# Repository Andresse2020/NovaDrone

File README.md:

# NovaDrone

Copyright © 2025 Andresse Brisel BASSINGA
Licensed under CERN Open Hardware Licence v2 – Weakly Reciprocal (CERN-OHL-W)

This project provides a complete hardware design for a professional UAV Quadcopter.
Firmware is proprietary and not covered by this licence.

## Project Overview
NovaDrone is a full hardware–firmware engineering project aiming to develop the **entire embedded electronics** of a quadcopter UAV **from scratch**.  
Rather than relying on off-the-shelf components, the project focuses on designing all critical subsystems: propulsion electronics, real-time motor control, power supervision, communication, diagnostics, and later, a fully custom flight controller.

The objective is to create a **professional-grade, reliable, and modular UAV platform** suitable for demanding embedded applications in robotics and aerospace.

---

## Key Features

- **Custom 1.5 kW Propulsion Board**  
  Single PCB integrating four 300–400 W ESCs and a dedicated supervisor MCU.

- **High-Performance ESC Subsystems**  
  STM32G4-based motor controllers using sensorless FOC, 48 kHz PWM, synchronized ADC sampling, and real-time telemetry.

- **Supervisor MCU**  
  Active precharge, power sequencing, battery monitoring, ARM/DISARM logic, watchdog, kill-line, USB monitoring, and DroneCAN communication.

- **Integrated Power Management**  
  LC filtering, TVS protection, OVP/UVLO/OCP/OTP, reinforced copper, and regulated 12 V / 5 V / 3.3 V rails.

- **Communication Architecture**  
  DroneCAN (CAN-FD) for propulsion telemetry and commands, UART CLI for debugging, USB streaming during development.

- **Custom Flight Controller (Next Stage)**  
  IMU fusion, stabilization, navigation logic, modular firmware architecture.

---

## Starting Point

NovaDrone uses a robust quadcopter frame as a mechanical platform for integration and testing:

- **Frame:** ZD550 carbon fiber  
- **Motors:** QM4208 brushless motors  
- **Propellers:** 1455 carbon fiber  

All electronics, power systems, and firmware are entirely custom-designed.

---

## Project Goals

NovaDrone aims to develop a **complete UAV electronics and firmware stack**, with emphasis on:

- High-efficiency propulsion and motor control  
- Intelligent and safe power management  
- Clean and maintainable firmware architecture  
- Robust diagnostics and system telemetry  
- Modular and scalable embedded design  
- Full control over every subsystem (no black boxes)

This is not a drone assembly project—**every subsystem is engineered from the ground up**.

---

## Architecture

### 1. Propulsion Board (1.5 kW)
A single PCB containing all propulsion-related electronics.

**Includes:**
- 4 × ESC (STM32G4)  
- 1 × Supervisor MCU  
- PSU: 12 V / 5 V / 3.3 V  
- Active precharge circuit  
- LC filtering, TVS, fuses  
- CAN-FD transceivers  
- USB and UART  
- XT60 (battery), XT30PW (motors), JST PH/SH, Tag-Connect SWD

---

### 2. ESC Subsystems (300–400 W each)

Each ESC is a fully independent motor controller.

**Features:**
- STM32G4 ARM Cortex-M4  
- Sensorless FOC  
- 48 kHz PWM  
- 24 kHz current loop  
- 1 kHz speed loop  
- Synchronized ADC sampling  
- Low-noise current sensing  
- Telemetry (current, voltage, RPM, temperature)  
- Bare-metal firmware (no HAL)

---

### 3. Supervisor MCU

Handles global power management and safety.

**Functions:**
- Active precharge (anti-inrush)  
- Battery voltage/current/temperature monitoring  
- Power sequencing  
- ARM/DISARM logic  
- Watchdog and kill-line  
- DroneCAN (CAN-FD) communication  
- **USB interface for development-time monitoring**  
- UART CLI  
- Planned: CAN bootloader

---

### 4. Integrated Power Management

Built directly into the propulsion board.

**Includes:**
- Input: LiPo 6S (18–25 V)  
- LC input filtering (PI filter)  
- TVS surge protection  
- OVP, UVLO, OCP, OTP protections  
- Reinforced copper planes  
- Regulated power rails (12 V / 5 V / 3.3 V)

---

### 5. Flight Control Unit (Upcoming)

The FCU will be developed after propulsion system validation.

**Planned capabilities:**
- STM32-based processing  
- IMU, barometer, magnetometer, GPS fusion  
- Kalman-based estimation  
- Stabilization loops  
- Trajectory and navigation control  

---

### 6. Communication System

| Interface | Purpose |
|-----------|---------|
| **DroneCAN (CAN-FD)** | ESC commands, propulsion telemetry, supervisor data |
| **USB** | High-rate logging and real-time monitoring during development |
| **UART CLI** | Debugging, tuning, calibration |
| **SWD** | Low-level flashing and debugging |

---

## Development Environment

NovaDrone firmware uses a custom modular embedded development environment built with **CMake**.

## Licence

Hardware design files are licensed under the CERN Open Hardware Licence v2 – Weakly Reciprocal (CERN-OHL-W).

The firmware is proprietary and not covered by this licence.
Commercial licences are available on request.

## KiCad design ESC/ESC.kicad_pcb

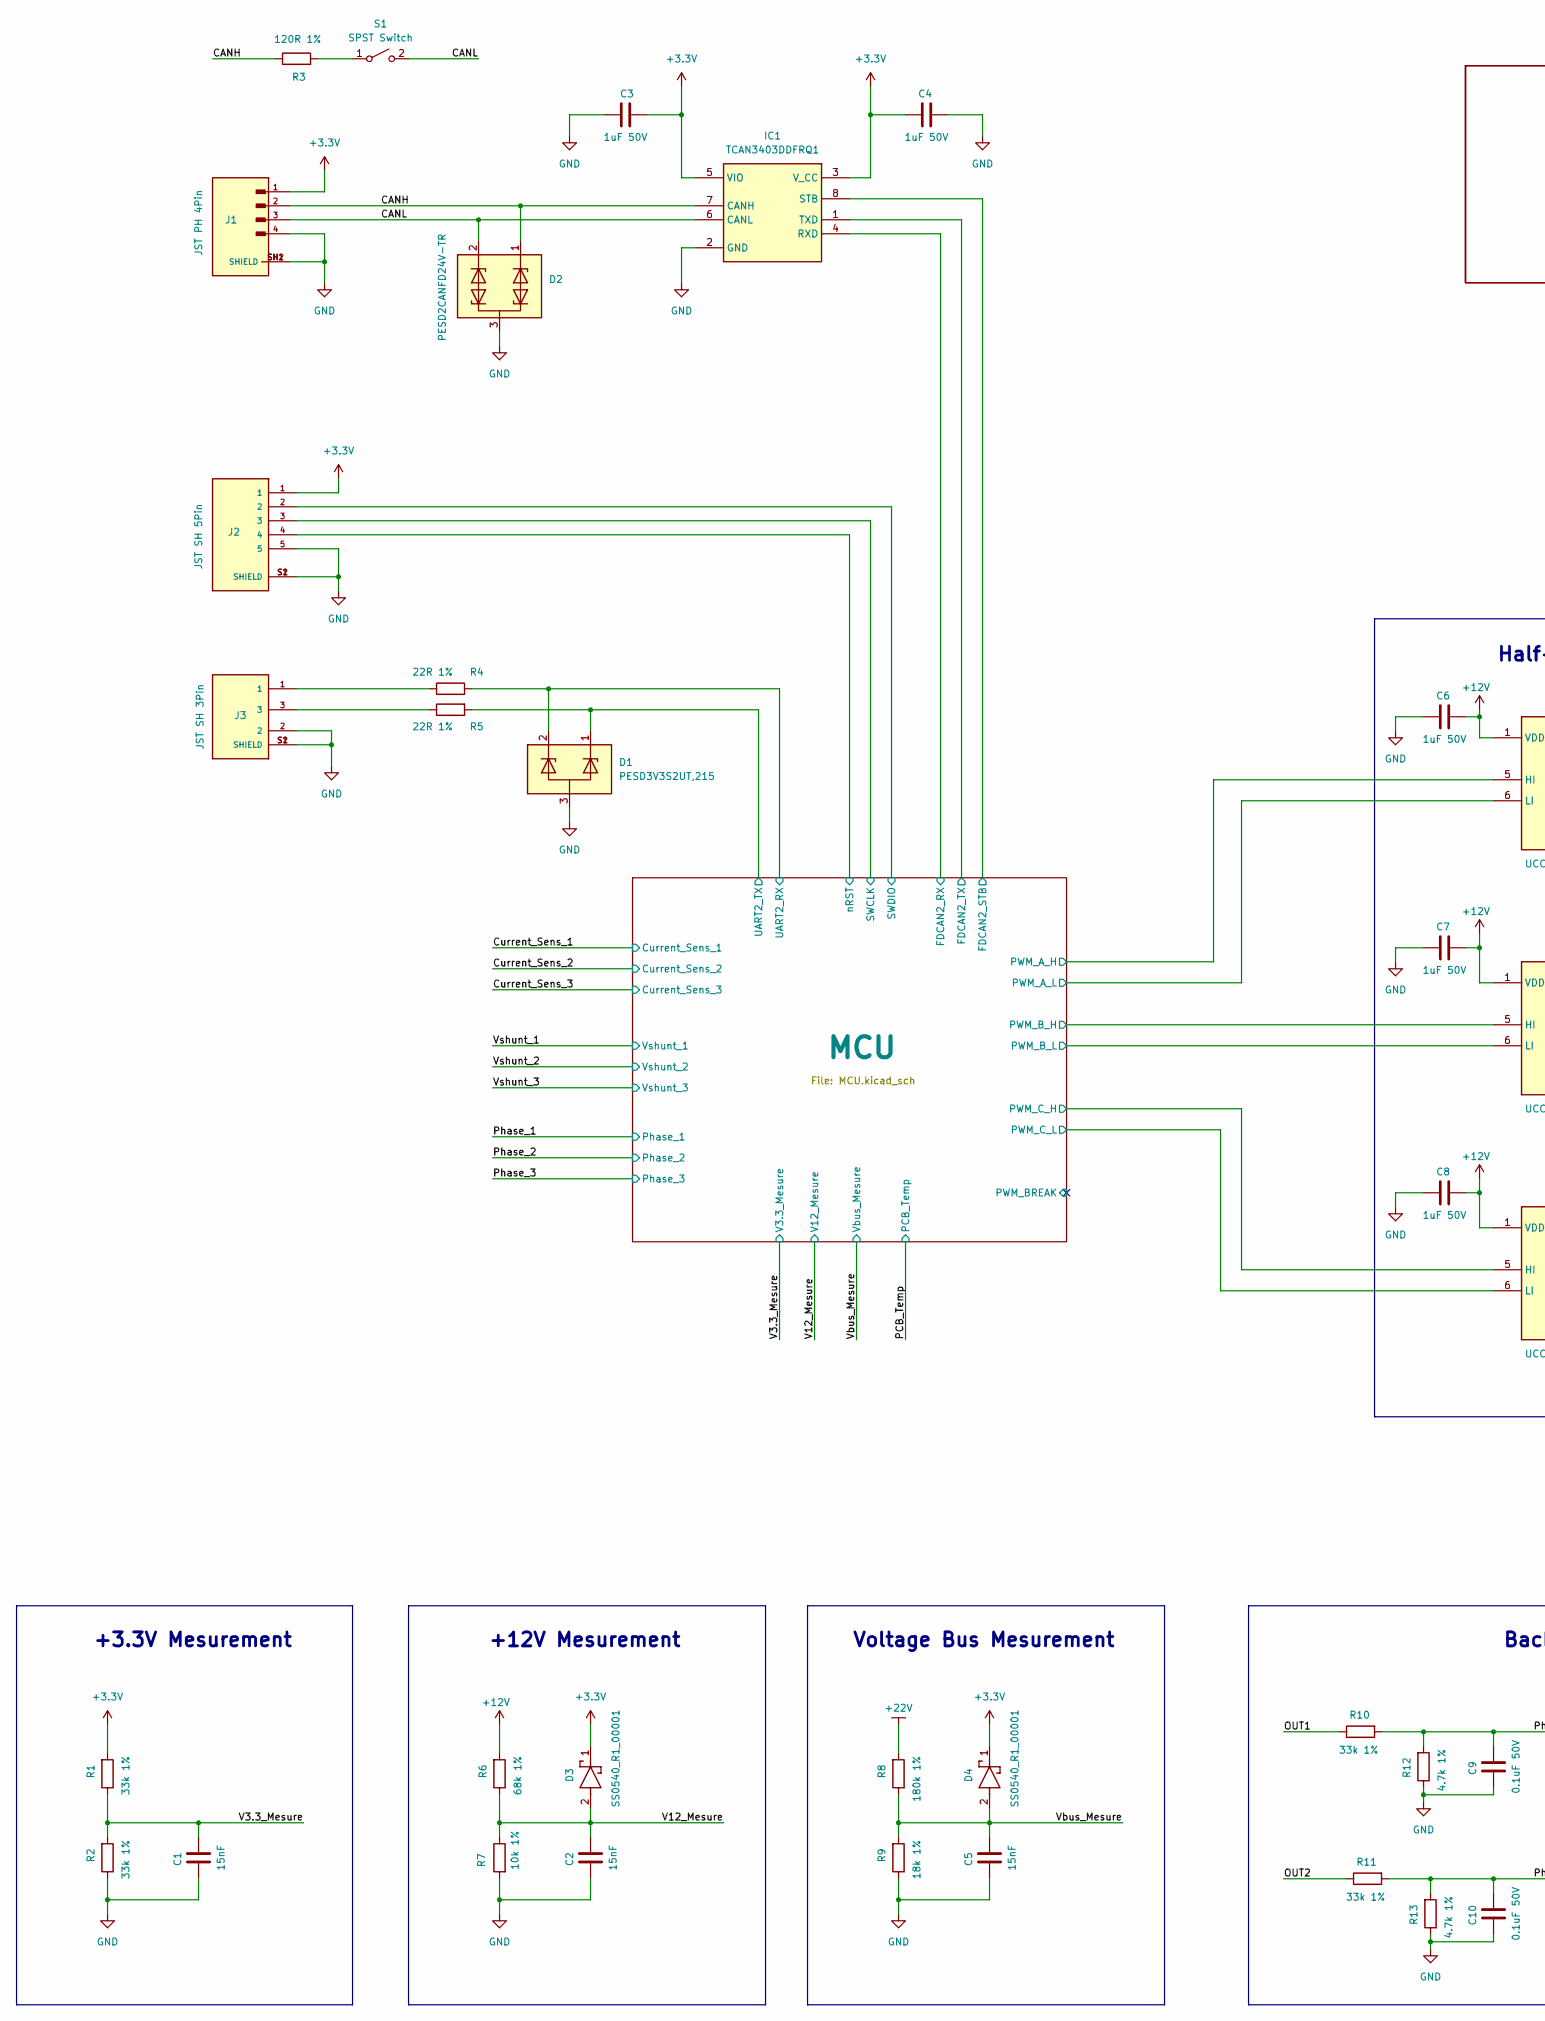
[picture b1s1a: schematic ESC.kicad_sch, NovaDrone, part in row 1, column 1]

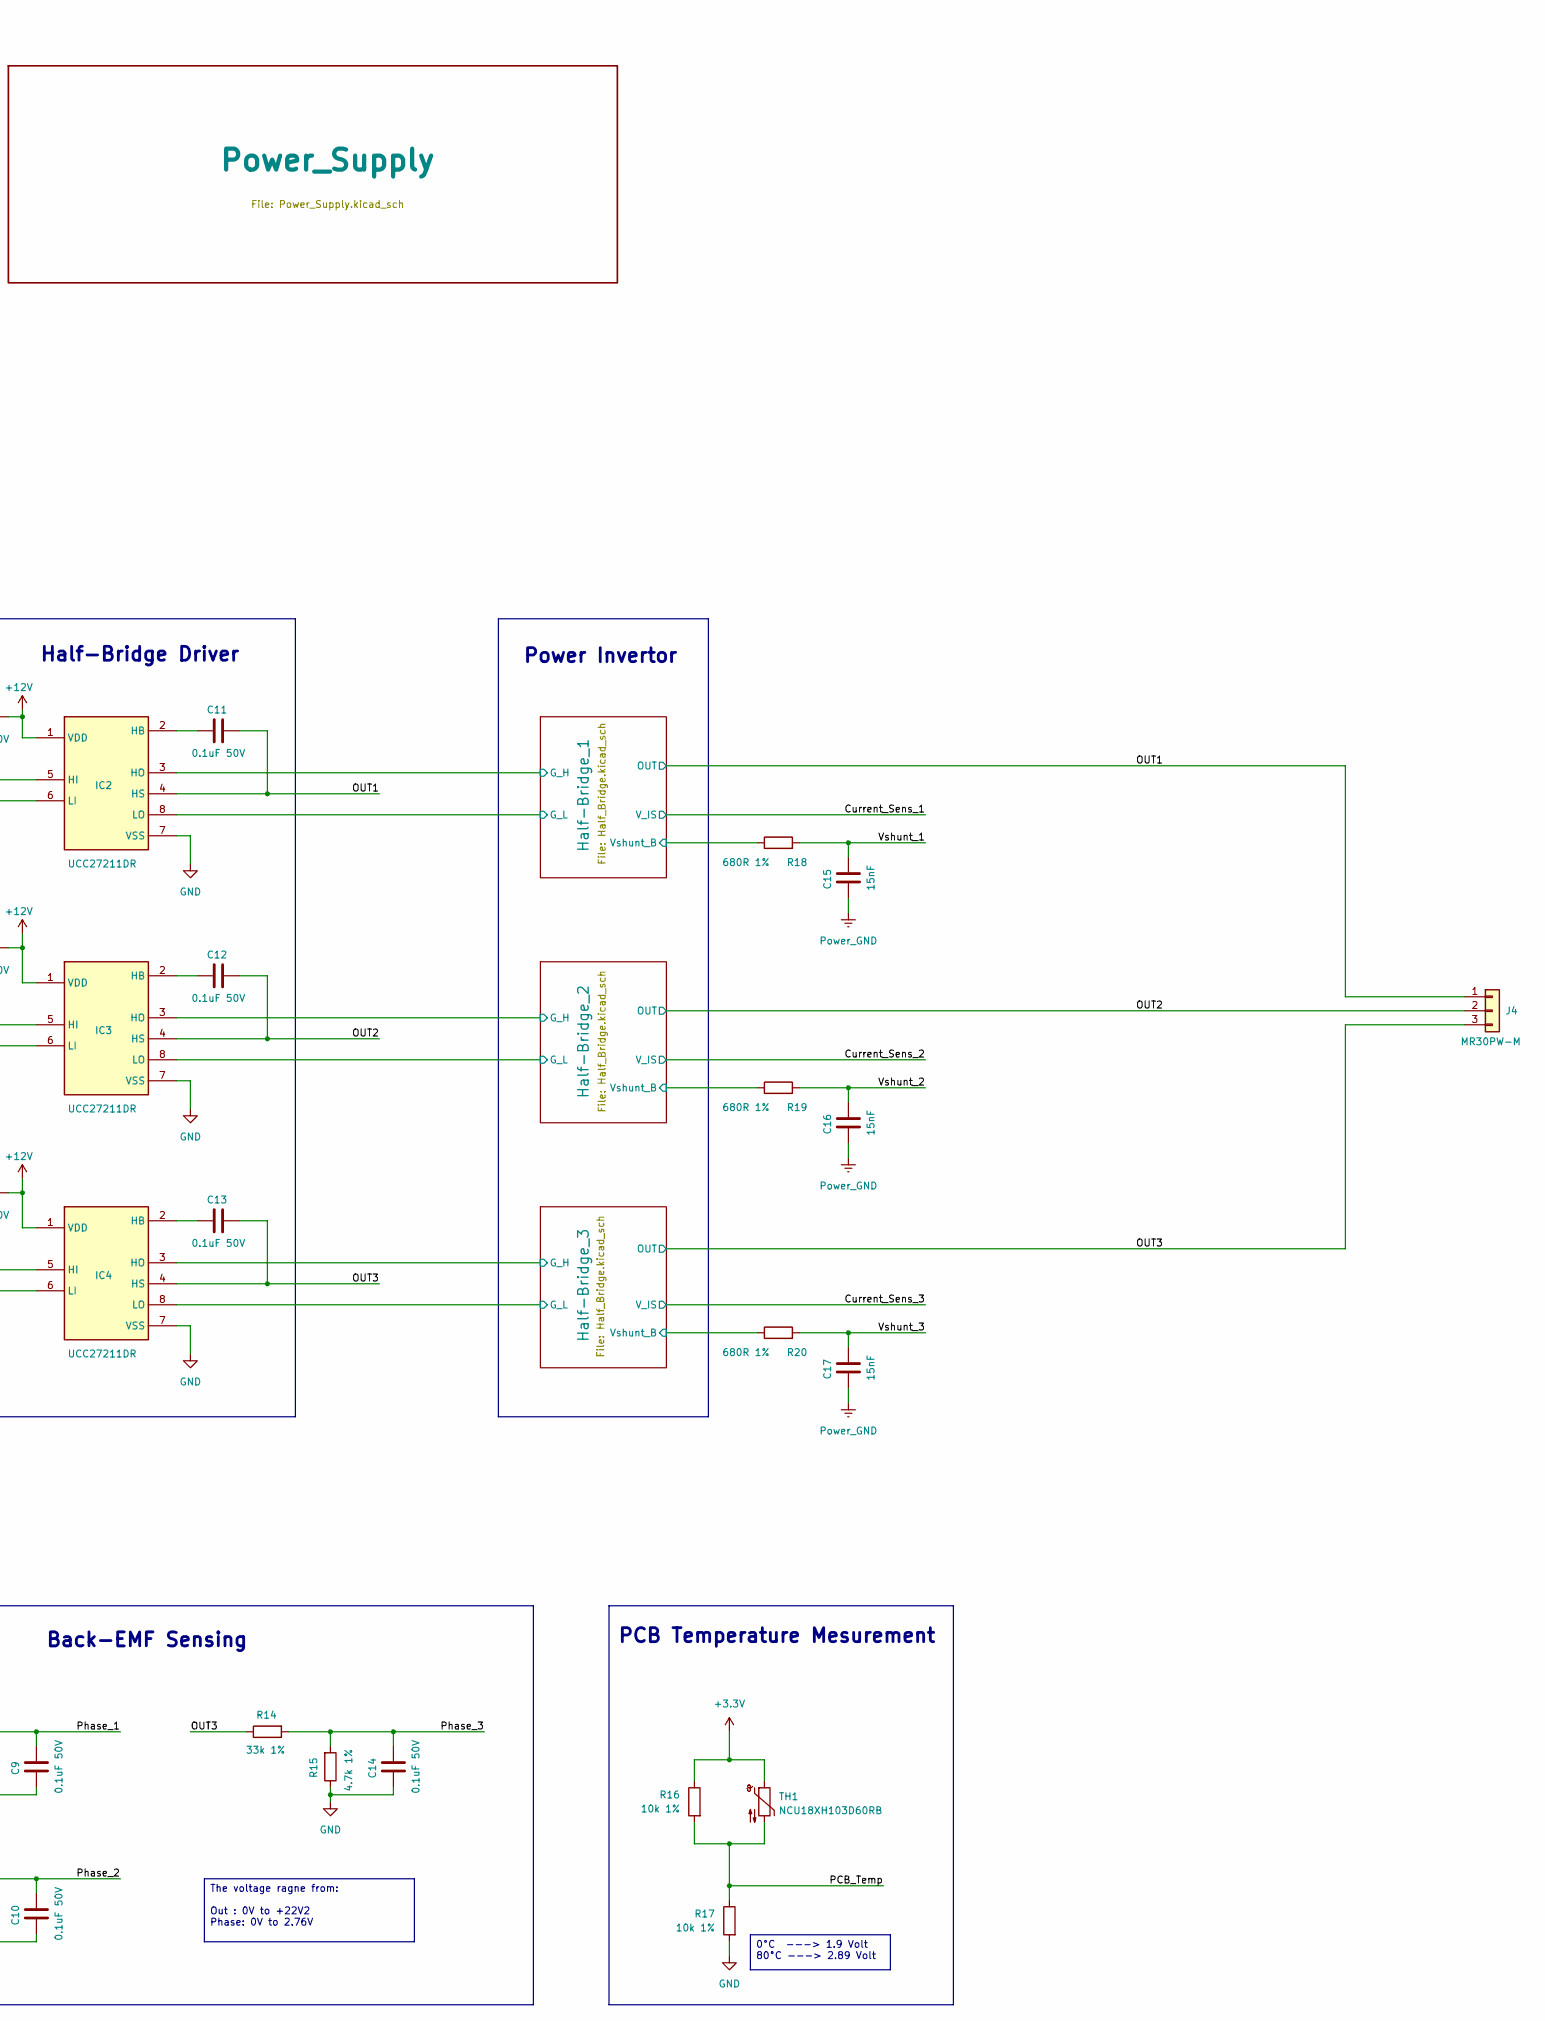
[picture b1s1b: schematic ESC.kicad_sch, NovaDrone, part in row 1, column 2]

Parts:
C1, C2, C5, C15, C16, C17: 15nF; C_0603_1608Metric; Manufacturer_Part_Number CL10B153KB8NNNC
C3, C4, C6, C7, C8: 1uF 50V; C_0805_2012Metric; Manufacturer_Part_Number CL21B105KBFNNNE
C9, C10, C11, C12, C13, C14: 0.1uF 50V; C_0603_1608Metric; Manufacturer_Part_Number CL10B104KB85PNL
D1: PESD3V3S2UT,215; SOT95P230X110-3N; Mouser Part Number 771-PESD3V3S2UT-T/R
D2: PESD2CANFD24V-TR; SOT95P230X110-3N; Mouser Part Number 771-PESD2CANFD24V-TR
D3, D4: SS0540_R1_00001; SOD3816X135N; Mouser Part Number 241-SS0540_R1_00001
IC1: TCAN3403DDFRQ1; SOT65P280X110-8N; Mouser Part Number 595-TCAN3403DDFRQ1
IC2, IC3, IC4: UCC27211DR; SOIC127P600X175-8N; Mouser Part Number 595-UCC27211DR
J1: JST PH 4Pin; S4B-PH-SM4-TB; Manufacturer_Part_Number S4B-PH-SM4-TB(LF)(SN)
J2: JST SH 5Pin; JST_BM05B-SRSS-TB_LF__SN_; PARTREV N/A
J3: JST SH 3Pin; JST_BM03B-SRSS-TB_LF__SN_; PARTREV N/A
J4: MR30PW-M; AMASS_MR30PW-M_1x03_P3.50mm_Horizontal
R1, R2, R10, R11, R14: 33k 1%; R_0603_1608Metric; Manufacturer_Part_Number AC0603FR-1333KL
R3: 120R 1%; R_0603_1608Metric; Manufacturer_Part_Number AC0603FR-07120RL
R4: 22R 1%; R_0603_1608Metric; Manufacturer_Part_Number AC0603FR-0722RL
R5: 22R 1%; R_0603_1608Metric; Manufacturer_Part_Number RT0603FRD0722RL
R6: 68k 1%; R_0603_1608Metric; Manufacturer_Part_Number RC0603FR-1068KL
R7, R16, R17: 10k 1%; R_0603_1608Metric; Manufacturer_Part_Number AF0603FR-0710KL
R8: 180k 1%; R_0603_1608Metric; Manufacturer_Part_Number RT0603FRE07180KL
R9: 18k 1%; R_0603_1608Metric; Manufacturer_Part_Number AC0603FR-1318KL
R12, R13, R15: 4.7k 1%; R_0603_1608Metric; Manufacturer_Part_Number AF0603FR-074K7L
R18, R19, R20: 680R 1%; R_0603_1608Metric; Manufacturer_Part_Number RC0603FR-07680RL
S1: SPST Switch; DS04254201BKSMT; Mouser Part Number 490-DS04254201BK-SMT
TH1: NCU18XH103D60RB; R_0603_1608Metric; Manufacturer_Part_Number NCU18XH103D60RB

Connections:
+3.3V: C3.1, C4.1, D3.1 (K), D4.1 (K), IC1.3 (V_CC), IC1.5 (VIO), J1.1, J2.1, R1.2, R16.1, TH1.1; also elsewhere on the board
+12V: C6.2, C7.2, C8.2, IC2.1 (VDD), IC3.1 (VDD), IC4.1 (VDD), R6.2; also elsewhere on the board
+22V: R8.2; also elsewhere on the board
/CANH: D2.1, IC1.7 (CANH), J1.2, R3.1
/CANL: D2.2, IC1.6 (CANL), J1.3, S1.2
/Half-Bridge_1/G_H: IC2.3 (HO); also elsewhere on the board
/Half-Bridge_1/G_L: IC2.8 (LO); also elsewhere on the board
/Half-Bridge_1/Vshunt_B: R18.1; also elsewhere on the board
/Half-Bridge_2/G_H: IC3.3 (HO); also elsewhere on the board
/Half-Bridge_2/G_L: IC3.8 (LO); also elsewhere on the board
/Half-Bridge_2/Vshunt_B: R19.1; also elsewhere on the board
/Half-Bridge_3/G_H: IC4.3 (HO); also elsewhere on the board
/Half-Bridge_3/G_L: IC4.8 (LO); also elsewhere on the board
/Half-Bridge_3/Vshunt_B: R20.1; also elsewhere on the board
/MCU/FDCAN2_RX: IC1.4 (RXD); also elsewhere on the board
/MCU/FDCAN2_STB: IC1.8 (STB); also elsewhere on the board
/MCU/FDCAN2_TX: IC1.1 (TXD); also elsewhere on the board
/MCU/PWM_A_H: IC2.5 (HI); also elsewhere on the board
/MCU/PWM_A_L: IC2.6 (LI); also elsewhere on the board
/MCU/PWM_B_H: IC3.5 (HI); also elsewhere on the board
/MCU/PWM_B_L: IC3.6 (LI); also elsewhere on the board
/MCU/PWM_C_H: IC4.5 (HI); also elsewhere on the board
/MCU/PWM_C_L: IC4.6 (LI); also elsewhere on the board
/MCU/SWCLK: J2.3; also elsewhere on the board
/MCU/SWDIO: J2.2; also elsewhere on the board
/MCU/UART2_RX: D1.2, R4.2; also elsewhere on the board
/MCU/UART2_TX: D1.1, R5.2; also elsewhere on the board
/MCU/nRST: J2.4; also elsewhere on the board
/OUT1: C11.2, IC2.4 (HS), J4.1, R10.1; also elsewhere on the board
/OUT2: C12.2, IC3.4 (HS), J4.2, R11.1; also elsewhere on the board
/OUT3: C13.2, IC4.4 (HS), J4.3, R14.1; also elsewhere on the board
/PCB_Temp: R16.2, R17.1, TH1.2; also elsewhere on the board
/Phase_1: C9.2, R10.2, R12.2; also elsewhere on the board
/Phase_2: C10.2, R11.2, R13.2; also elsewhere on the board
/Phase_3: C14.2, R14.2, R15.2; also elsewhere on the board
/V3.3_Mesure: C1.2, R1.1, R2.2; also elsewhere on the board
/V12_Mesure: C2.2, D3.2 (A), R6.1, R7.1; also elsewhere on the board
/Vbus_Mesure: C5.2, D4.2 (A), R8.1, R9.2; also elsewhere on the board
/Vshunt_1: C15.2, R18.2; also elsewhere on the board
/Vshunt_2: C16.2, R19.2; also elsewhere on the board
/Vshunt_3: C17.2, R20.2; also elsewhere on the board
GND: C1.1, C2.1, C3.2, C4.2, C5.1, C6.1, C7.1, C8.1, C9.1, C10.1, C14.1, C15.1, C16.1, C17.1, D1.3, D2.3, IC1.2 (GND), IC2.7 (VSS), IC3.7 (VSS), IC4.7 (VSS), J1.4, J1.SH1 (SHIELD), J1.SH2 (SHIELD), J2.5, J2.S1 (SHIELD), J2.S2 (SHIELD), J3.2, J3.S1 (SHIELD), J3.S2 (SHIELD), R2.1, R7.2, R9.1, R12.1, R13.1, R15.1, R17.2; also elsewhere on the board
unnamed: C11.1, IC2.2 (HB)
unnamed: C12.1, IC3.2 (HB)
unnamed: C13.1, IC4.2 (HB)
unnamed: J3.1, R4.1
unnamed: J3.3, R5.1
unnamed: R3.2, S1.1

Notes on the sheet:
Voltage Bus Mesurement
Back-EMF Sensing
PCB Temperature Mesurement
Power Invertor
+3.3V Mesurement
+12V Mesurement
Half-Bridge Driver
0°C ---> 1.9 Volt 80°C ---> 2.89 Volt
The voltage ragne from: Out : 0V to +22V2 Phase: 0V to 2.76V

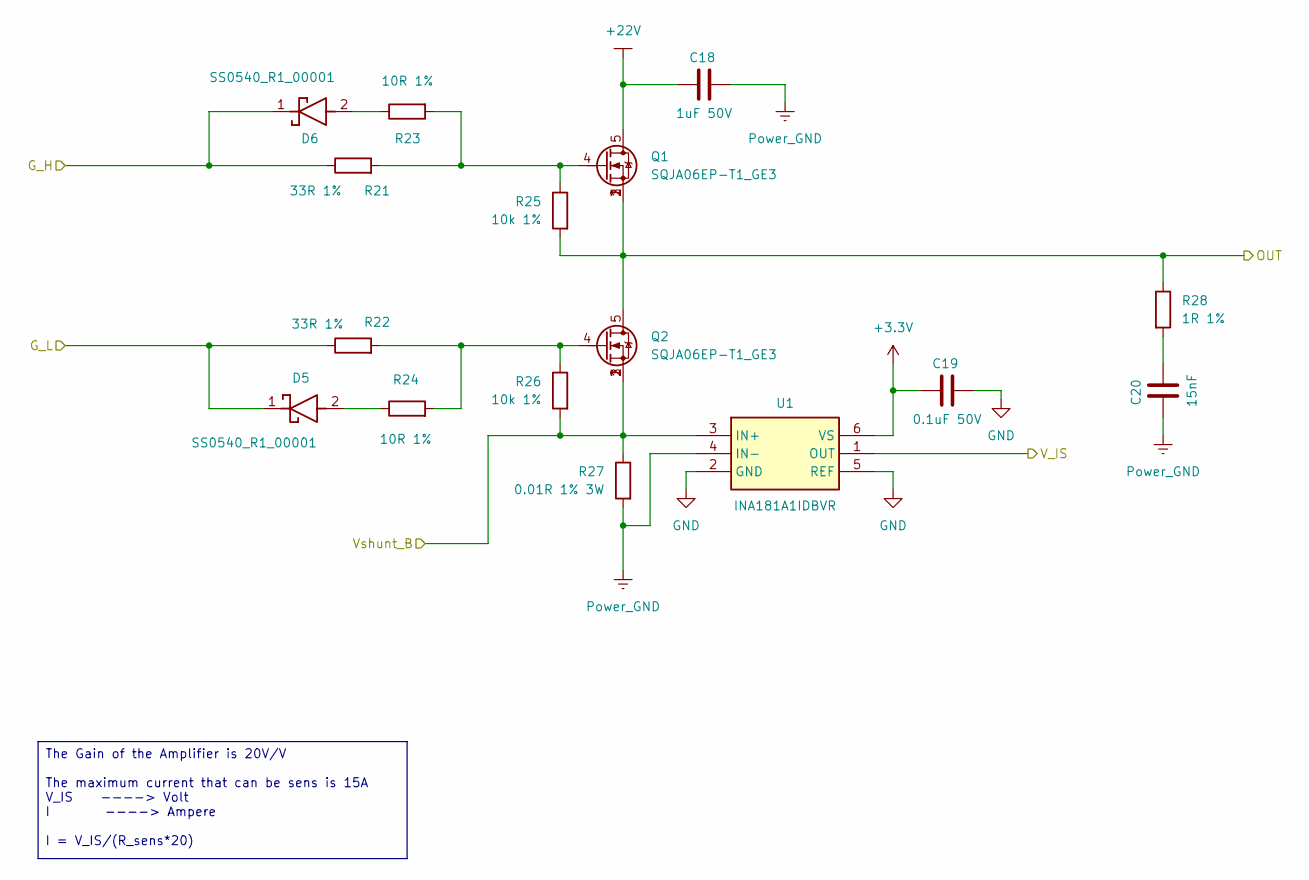
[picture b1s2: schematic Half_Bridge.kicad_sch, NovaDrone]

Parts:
C18: 1uF 50V; C_0805_2012Metric; Manufacturer_Part_Number CL21B105KBFNNNE
C19: 0.1uF 50V; C_0603_1608Metric; Manufacturer_Part_Number CL10B104KB85PNL
C20: 15nF; C_0603_1608Metric; Manufacturer_Part_Number CL10B153KB8NNNC
D5, D6: SS0540_R1_00001; SOD3816X135N; Mouser Part Number 241-SS0540_R1_00001
Q1, Q2: SQJA06EP-T1_GE3; PowerPAK_SO-8L_Single; Manufacturer_Part_Number SQJA06EP-T1_GE3
R21, R22: 33R 1%; R_0603_1608Metric; Manufacturer_Part_Number AF0603FR-0733RL
R23, R24: 10R 1%; R_0603_1608Metric; Manufacturer_Part_Number RE0603FRE0710RL
R25, R26: 10k 1%; R_0603_1608Metric; Manufacturer_Part_Number AF0603FR-0710KL
R27: 0.01R 1% 3W; R_2512_6332Metric; Manufacturer_Part_Number PA2512FKE7T0R01E
R28: 1R 1%; R_0603_1608Metric; Manufacturer_Part_Number AF0603FR-071RL
U1: INA181A1IDBVR; SOT95P280X145-6N; Mouser Part Number 595-INA181A1IDBVR

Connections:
+3.3V: C19.1, U1.6 (VS); also elsewhere on the board
+22V: C18.1, Q1.5; also elsewhere on the board
/Current_Sens_1: U1.1 (OUT); also elsewhere on the board
/Half-Bridge_1/G_H: D6.1 (K), R21.1; also elsewhere on the board
/Half-Bridge_1/G_L: D5.1 (K), R22.1; also elsewhere on the board
/Half-Bridge_1/Vshunt_B: Q2.1, Q2.2, Q2.3, R26.2, R27.1, U1.3 (IN+); also elsewhere on the board
/OUT1: Q1.1, Q1.2, Q1.3, Q2.5, R25.2, R28.1; also elsewhere on the board
GND: C18.2, C19.2, C20.1, R27.2, U1.2 (GND), U1.4 (IN-), U1.5 (REF); also elsewhere on the board
unnamed: C20.2, R28.2
unnamed: D5.2 (A), R24.1
unnamed: D6.2 (A), R23.1
unnamed: Q1.4, R21.2, R23.2, R25.1
unnamed: Q2.4, R22.2, R24.2, R26.1

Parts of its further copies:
C21, C24: 1uF 50V; C_0805_2012Metric; Manufacturer_Part_Number CL21B105KBFNNNE
C22, C25: 0.1uF 50V; C_0603_1608Metric; Manufacturer_Part_Number CL10B104KB85PNL
C23, C26: 15nF; C_0603_1608Metric; Manufacturer_Part_Number CL10B153KB8NNNC
D7, D8, D9, D10: SS0540_R1_00001; SOD3816X135N; Mouser Part Number 241-SS0540_R1_00001
Q3, Q4, Q5, Q6: SQJA06EP-T1_GE3; PowerPAK_SO-8L_Single; Manufacturer_Part_Number SQJA06EP-T1_GE3
R29, R30, R37, R38: 33R 1%; R_0603_1608Metric; Manufacturer_Part_Number AF0603FR-0733RL
R31, R32, R39, R40: 10R 1%; R_0603_1608Metric; Manufacturer_Part_Number RE0603FRE0710RL
R33, R34, R41, R42: 10k 1%; R_0603_1608Metric; Manufacturer_Part_Number AF0603FR-0710KL
R35, R43: 0.01R 1% 3W; R_2512_6332Metric; Manufacturer_Part_Number PA2512FKE7T0R01E
R36, R44: 1R 1%; R_0603_1608Metric; Manufacturer_Part_Number AF0603FR-071RL
U2, U3: INA181A1IDBVR; SOT95P280X145-6N; Mouser Part Number 595-INA181A1IDBVR

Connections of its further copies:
+3.3V: C22.1, C25.1, U2.6 (VS), U3.6 (VS); also elsewhere on the board
+22V: C21.1, C24.1, Q3.5, Q5.5; also elsewhere on the board
/Current_Sens_2: U3.1 (OUT); also elsewhere on the board
/Current_Sens_3: U2.1 (OUT); also elsewhere on the board
/Half-Bridge_2/G_H: D10.1 (K), R37.1; also elsewhere on the board
/Half-Bridge_2/G_L: D9.1 (K), R38.1; also elsewhere on the board
/Half-Bridge_2/Vshunt_B: Q6.1, Q6.2, Q6.3, R42.2, R43.1, U3.3 (IN+); also elsewhere on the board
/Half-Bridge_3/G_H: D8.1 (K), R29.1; also elsewhere on the board
/Half-Bridge_3/G_L: D7.1 (K), R30.1; also elsewhere on the board
/Half-Bridge_3/Vshunt_B: Q4.1, Q4.2, Q4.3, R34.2, R35.1, U2.3 (IN+); also elsewhere on the board
/OUT2: Q5.1, Q5.2, Q5.3, Q6.5, R41.2, R44.1; also elsewhere on the board
/OUT3: Q3.1, Q3.2, Q3.3, Q4.5, R33.2, R36.1; also elsewhere on the board
GND: C21.2, C22.2, C23.1, C24.2, C25.2, C26.1, R35.2, R43.2, U2.2 (GND), U2.4 (IN-), U2.5 (REF), U3.2 (GND), U3.4 (IN-), U3.5 (REF); also elsewhere on the board
unnamed: C23.2, R36.2
unnamed: C26.2, R44.2
unnamed: D7.2 (A), R32.1
unnamed: D8.2 (A), R31.1
unnamed: D9.2 (A), R40.1
unnamed: D10.2 (A), R39.1
unnamed: Q3.4, R29.2, R31.2, R33.1
unnamed: Q4.4, R30.2, R32.2, R34.1
unnamed: Q5.4, R37.2, R39.2, R41.1
unnamed: Q6.4, R38.2, R40.2, R42.1

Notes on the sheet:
The Gain of the Amplifier is 20V/V The maximum current that can be sens is 15A V_IS ----> Volt I ----> Ampere I = V_IS/(R_sens*20)

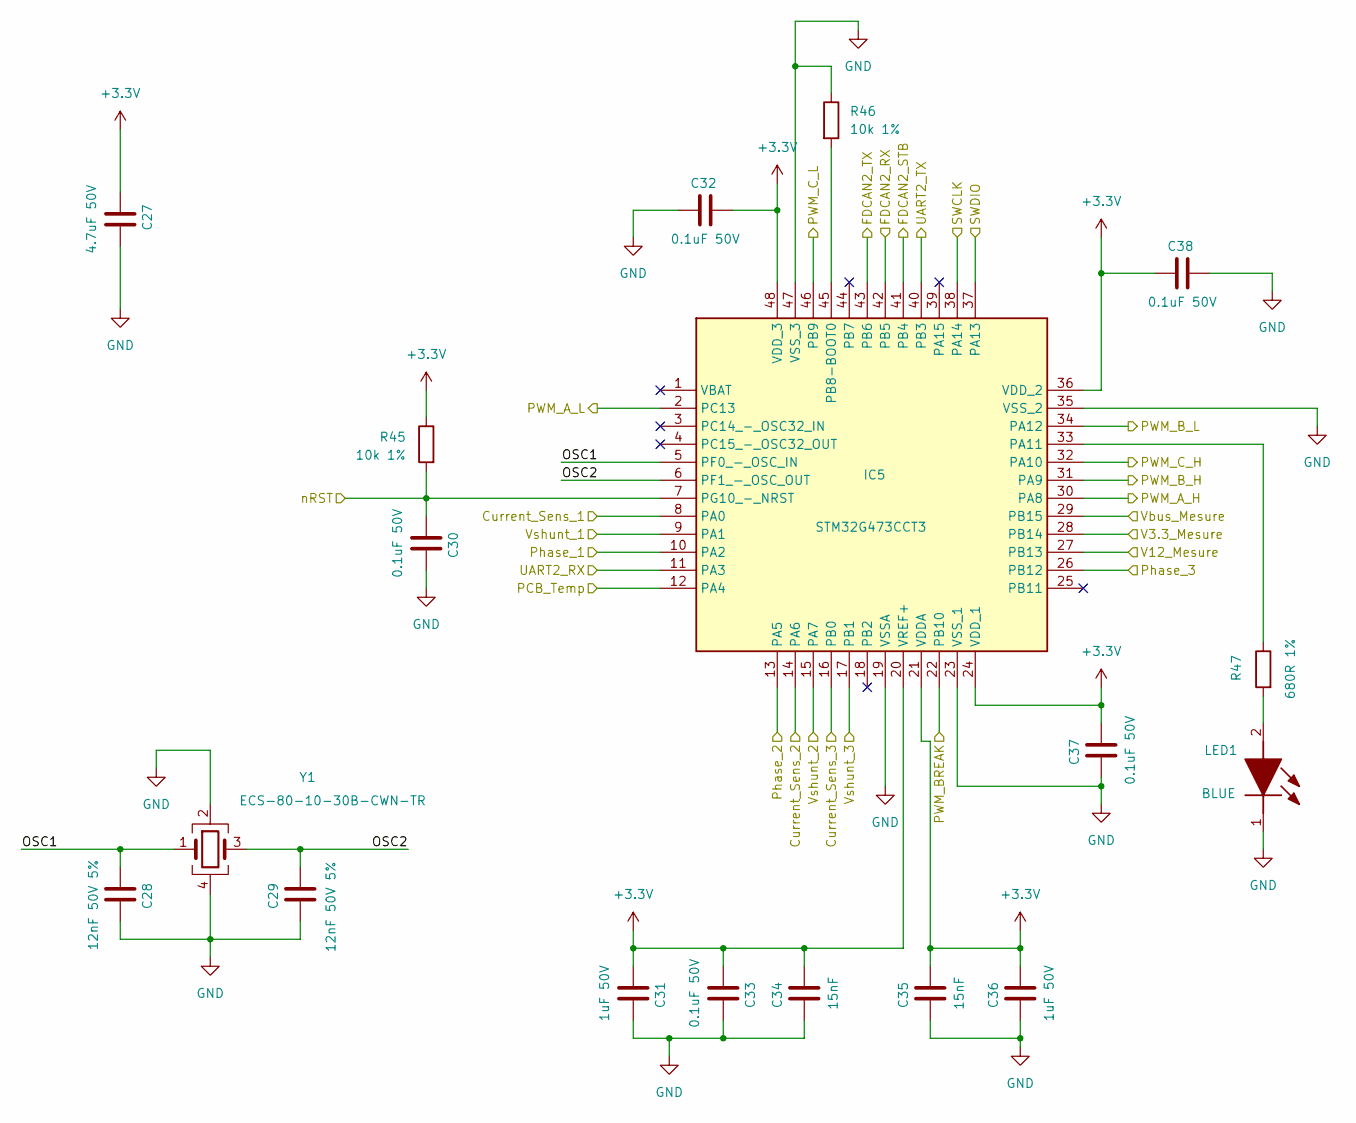
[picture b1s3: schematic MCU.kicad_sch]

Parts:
C27: 4.7uF 50V; C_1206_3216Metric; Manufacturer_Part_Number CL31B475KBHNFNE
C28, C29: 12nF 50V 5%; C_0603_1608Metric; Manufacturer_Part_Number 06035C120J4T2A
C30, C32, C33, C37, C38: 0.1uF 50V; C_0603_1608Metric; Manufacturer_Part_Number CL10B104KB85PNL
C31, C36: 1uF 50V; C_0805_2012Metric; Manufacturer_Part_Number CL21B105KBFNNNE
C34, C35: 15nF; C_0603_1608Metric; Manufacturer_Part_Number CL10B153KB8NNNC
IC5: STM32G473CCT3; QFP50P900X900X160-48N; Mouser Part Number 511-STM32G473CCT3
LED1: BLUE; LEDM168X80N; Mouser Part Number 604-APHD1608LQBCD
R45, R46: 10k 1%; R_0603_1608Metric; Manufacturer_Part_Number AF0603FR-0710KL
R47: 680R 1%; R_0603_1608Metric; Manufacturer_Part_Number RC0603FR-07680RL
Y1: ECS-80-10-30B-CWN-TR; ECS801830BAGNTR; Mouser Part Number 520-80-10-30B-CWNT

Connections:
+3.3V: C27.1, C31.2, C32.2, C33.2, C34.2, C35.2, C36.2, C37.2, C38.1, IC5.20 (VREF+), IC5.21 (VDDA), IC5.24 (VDD_1), IC5.36 (VDD_2), IC5.48 (VDD_3), R45.1; also elsewhere on the board
/Current_Sens_1: IC5.8 (PA0); also elsewhere on the board
/Current_Sens_2: IC5.14 (PA6); also elsewhere on the board
/Current_Sens_3: IC5.16 (PB0); also elsewhere on the board
/MCU/FDCAN2_RX: IC5.42 (PB5); also elsewhere on the board
/MCU/FDCAN2_STB: IC5.41 (PB4); also elsewhere on the board
/MCU/FDCAN2_TX: IC5.43 (PB6); also elsewhere on the board
/MCU/OSC1: C28.2, IC5.5 (PF0_-_OSC_IN), Y1.1
/MCU/OSC2: C29.2, IC5.6 (PF1_-_OSC_OUT), Y1.3
/MCU/PWM_A_H: IC5.30 (PA8); also elsewhere on the board
/MCU/PWM_A_L: IC5.2 (PC13); also elsewhere on the board
/MCU/PWM_BREAK: IC5.22 (PB10)
/MCU/PWM_B_H: IC5.31 (PA9); also elsewhere on the board
/MCU/PWM_B_L: IC5.34 (PA12); also elsewhere on the board
/MCU/PWM_C_H: IC5.32 (PA10); also elsewhere on the board
/MCU/PWM_C_L: IC5.46 (PB9); also elsewhere on the board
/MCU/SWCLK: IC5.38 (PA14); also elsewhere on the board
/MCU/SWDIO: IC5.37 (PA13); also elsewhere on the board
/MCU/UART2_RX: IC5.11 (PA3); also elsewhere on the board
/MCU/UART2_TX: IC5.40 (PB3); also elsewhere on the board
/MCU/nRST: C30.2, IC5.7 (PG10_-_NRST), R45.2; also elsewhere on the board
/PCB_Temp: IC5.12 (PA4); also elsewhere on the board
/Phase_1: IC5.10 (PA2); also elsewhere on the board
/Phase_2: IC5.13 (PA5); also elsewhere on the board
/Phase_3: IC5.26 (PB12); also elsewhere on the board
/V3.3_Mesure: IC5.28 (PB14); also elsewhere on the board
/V12_Mesure: IC5.27 (PB13); also elsewhere on the board
/Vbus_Mesure: IC5.29 (PB15); also elsewhere on the board
/Vshunt_1: IC5.9 (PA1); also elsewhere on the board
/Vshunt_2: IC5.15 (PA7); also elsewhere on the board
/Vshunt_3: IC5.17 (PB1); also elsewhere on the board
GND: C27.2, C28.1, C29.1, C30.1, C31.1, C32.1, C33.1, C34.1, C35.1, C36.1, C37.1, C38.2, IC5.19 (VSSA), IC5.23 (VSS_1), IC5.35 (VSS_2), IC5.47 (VSS_3), LED1.1 (K), R46.1, Y1.2, Y1.4; also elsewhere on the board
unnamed: IC5.33 (PA11), R47.1
unnamed: IC5.45 (PB8-BOOT0), R46.2
unnamed: LED1.2 (A), R47.2

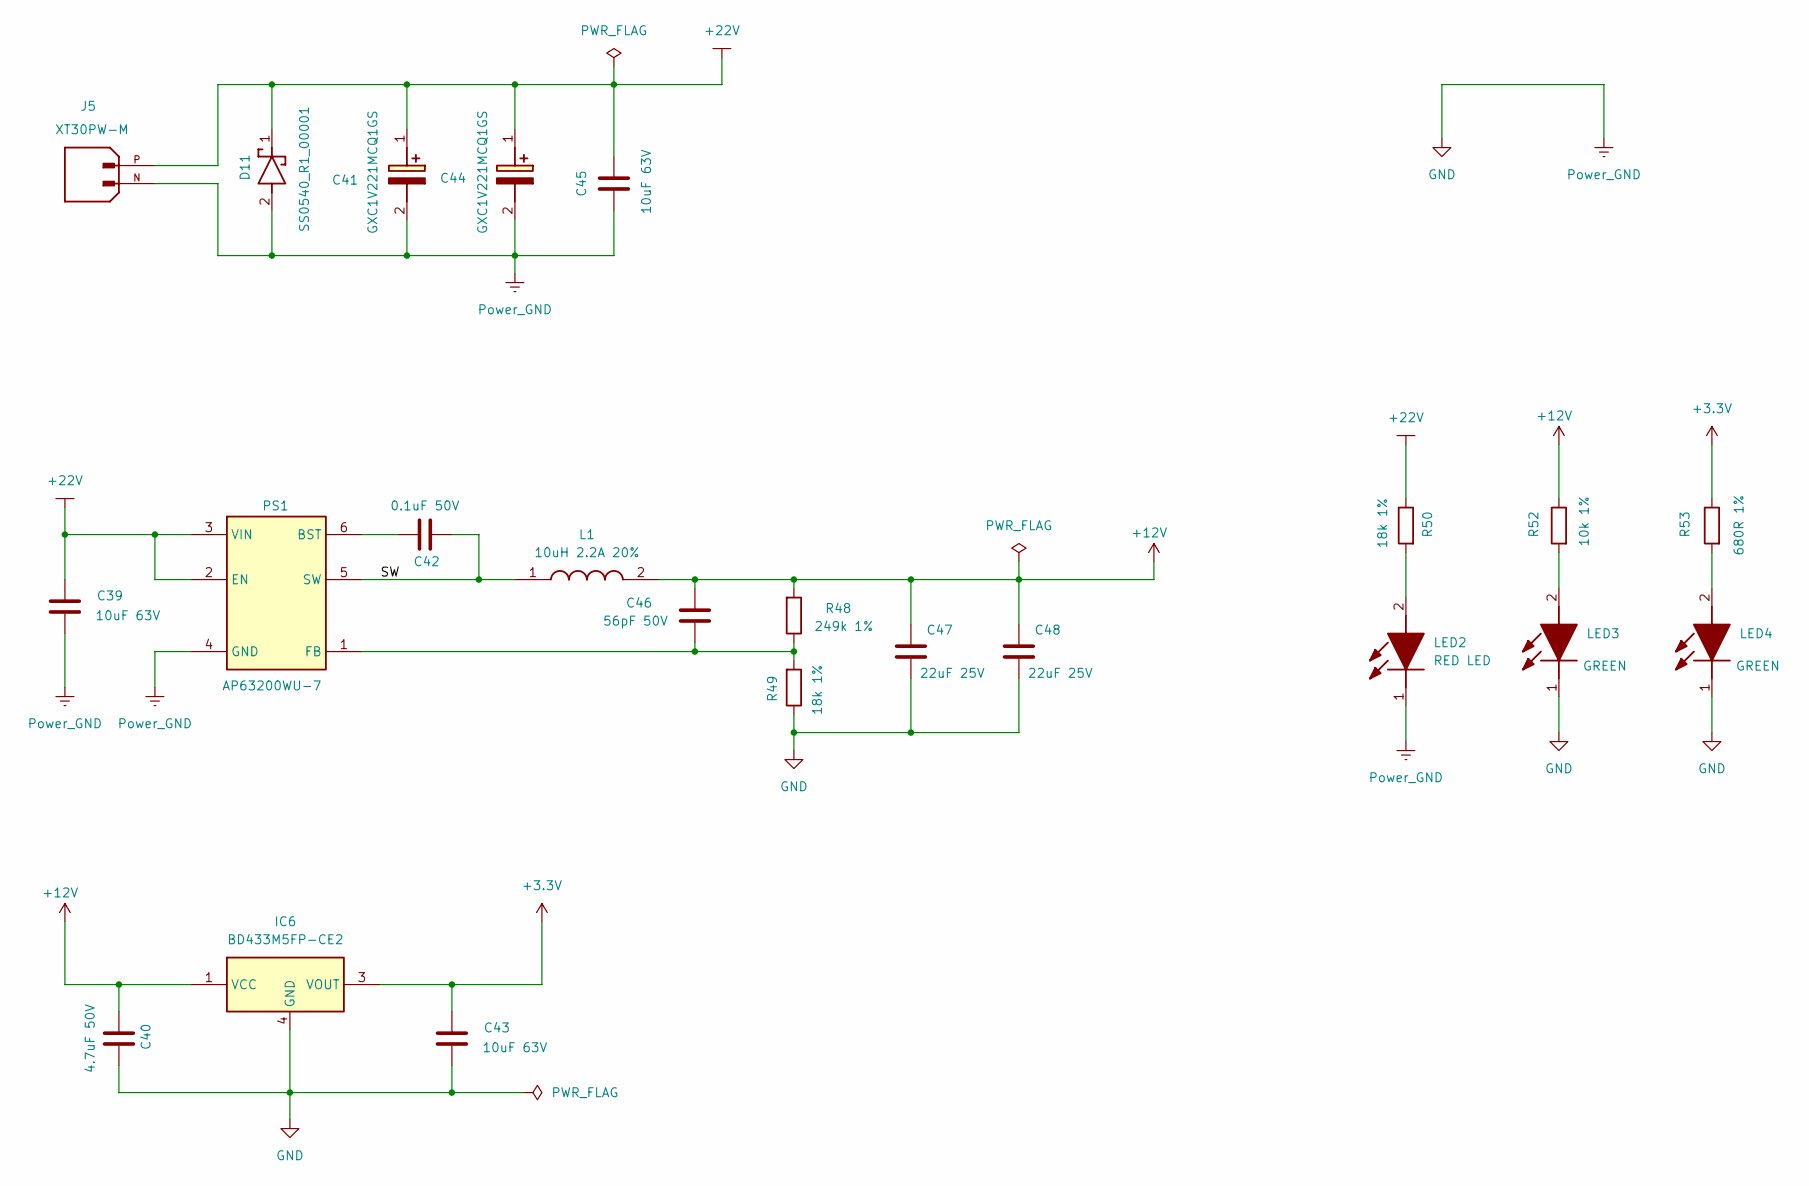
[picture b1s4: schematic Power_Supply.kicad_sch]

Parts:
C39, C43, C45: 10uF 63V; C_1210_3225Metric; Manufacturer_Part_Number CL32B106KMVNNWE
C40: 4.7uF 50V; C_1206_3216Metric; Manufacturer_Part_Number CL31B475KBHNFNE
C41, C44: GXC1V221MCQ1GS; CAPAE1030X1080N; Mouser Part Number 647-GXC1V221MCQ1GS
C42: 0.1uF 50V; C_0603_1608Metric; Manufacturer_Part_Number CL10B104KB85PNL
C46: 56pF 50V; C_0603_1608Metric; Manufacturer_Part_Number CL10C560JB8NNNC
C47, C48: 22uF 25V; C_1210_3225Metric; Manufacturer_Part_Number CL32B226KAJNNNE
D11: SS0540_R1_00001; SOD3816X135N; Mouser Part Number 241-SS0540_R1_00001
IC6: BD433M5FP-CE2; BD433M5FPCE2; Mouser Part Number 755-BD433M5FP-CE2
J5: XT30PW-M; AMASS_XT30PW-M; PARTREV 1.2
L1: 10uH 2.2A 20%; BWVS00505040100M00; Manufacturer_Part_Number BWVS00505040100M00
LED2: RED LED; LEDM168X80N; Manufacturer_Part_Number APHD1608LSURCK
LED3, LED4: GREEN; LEDM168X80N; Mouser Part Number 604-APHD1608LZGCK
PS1: AP63200WU-7; SOT95P280X100-6N; Mouser Part Number 621-AP63200WU-7
R48: 249k 1%; R_0603_1608Metric; Manufacturer_Part_Number AF0603FR-07249KL
R49, R50: 18k 1%; R_0603_1608Metric; Manufacturer_Part_Number AC0603FR-1318KL
R52: 10k 1%; R_0603_1608Metric; Manufacturer_Part_Number AF0603FR-0710KL
R53: 680R 1%; R_0603_1608Metric; Manufacturer_Part_Number RC0603FR-07680RL

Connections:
+3.3V: C43.2, IC6.3 (VOUT), R53.1; also elsewhere on the board
+12V: C40.1, C46.2, C47.2, C48.2, IC6.1 (VCC), L1.2, R48.2, R52.1; also elsewhere on the board
+22V: C39.2, C41.1 (+), C44.1 (+), C45.2, D11.1 (K), J5.P, PS1.2 (EN), PS1.3 (VIN), R50.1; also elsewhere on the board
/Power_Supply/SW: C42.1, L1.1, PS1.5 (SW)
GND: C39.1, C40.2, C41.2 (-), C43.1, C44.2 (-), C45.1, C47.1, C48.1, D11.2 (A), IC6.4 (GND), J5.N, LED2.1 (K), LED3.1 (K), LED4.1 (K), PS1.4 (GND), R49.1; also elsewhere on the board
unnamed: LED2.2 (A), R50.2
unnamed: LED3.2 (A), R52.2
unnamed: LED4.2 (A), R53.2
unnamed: C42.2, PS1.6 (BST)
unnamed: C46.1, PS1.1 (FB), R48.1, R49.2
